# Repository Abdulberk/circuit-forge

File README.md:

<div align="center">

# ⚡ Circuit Forge

**AI-assisted circuit design, verified by real SPICE.**
Every verdict is backed by measured evidence — never by a model's say-so.

[Quick start](#-quick-start) · [What it does](#-what-it-does) · [Architecture](#%EF%B8%8F-architecture) · [Quality](#-tested-against-real-ngspice--in-ci) · [Docs](#-documentation) · [Status](#%EF%B8%8F-status--roadmap)

</div>

---

Most AI tools *tell* you a circuit works. **Circuit Forge proves it.** A design is only called
**verified** after real **ngspice** simulates it and every stated acceptance criterion is checked
against *measured* values — voltages, branch currents, cutoff frequency, THD, gain. What you get
back is not "looks good": it is an evidence pack.

```jsonc
// POST /verify-design → DesignEvidence (truncated)
{
  "verdict": "pass",
  "summary": "Simulation OK — 3/3 checks passed",
  "assertions": [
    {
      "label": "LED current ≈ 10 mA",
      "probe": "i(R1)", "metric": "final", "op": "approx",
      "target": 0.01, "actual": 0.0091, "pass": true,
      "detail": "final(i(R1)) = 0.0091 ✓ approx 0.01"
    }
    // …every criterion, with the measured value and its signed distance to target
  ],
  "measurements": [ { "node": "@r1[i]", "min": 0.0091, "max": 0.0091, "final": 0.0091 } /* … */ ],
  "robustness": {
    "worstCase": { "componentsCornered": ["R1"], "evaluated": 2, "passed": 2, "passAllCorners": true }
  }
}
```

> **Heads up — this repo is pnpm-only.** Internal packages use the `workspace:*` protocol, which
> `npm install` cannot parse. Always use `pnpm`. See [LOCAL_SETUP.md](LOCAL_SETUP.md).

---

## ✨ What it does

| | Capability |
|---|---|
| 🧠 **AI design loop** | Describe intent → the LLM designs against a **live parts catalog** (real MPNs + sourcing), simulates, reads the measured failures, and self-repairs until the spec is met — or honestly reports why not. |
| ✅ **Deterministic verification** | Circuit JSON → generated SPICE netlist → sandboxed ngspice → typed results → pass/fail per acceptance criterion (`min · max · final · pp · avg · rms · cutoff · thd · gain`). |
| 🎲 **Robustness, not just nominal** | Monte-Carlo yield with confidence interval, worst-case ±tolerance **corner analysis** (2ᵏ extremes), and parametric sweeps — a design that only works at nominal isn't a design. |
| 📈 **Broad analysis coverage** | Operating point, transient, AC, DC sweep, noise, DC sensitivity — plus Fourier/THD, `.meas` measurements, and small-signal transfer function. |
| 🔀 **Mixed-signal** | Digital XSPICE devices (gates, flip-flops, latches, tristate) auto-bridged to the analog domain. |
| 🔁 **SPICE interchange** | Import/export standard SPICE decks (LTspice/KiCad round-trip), analog and digital. |
| 🧩 **Real components** | TME-backed catalog search over 1.3M+ manufacturer parts (stock, pricing, datasheets), E-series (IEC 60063) value snapping, per-version **BOM** export. |
| 🖨️ **PCB pipeline** | Autorouted layout, KiCad-based DRC, Gerber / BOM / pick-and-place export, and a 3D board model (GLB) — as an async job queue. |
| 🏢 **Multi-tenant platform** | Orgs & RBAC, JWT auth, usage metering + quotas, platform-admin API with audit trail, OpenTelemetry observability (opt-in), readiness probes. |

---

## 🏗️ Architecture

The heart of the system is a **closed feedback cycle**: design → simulate → measure → repair.
Every netlist runs in a **sandboxed subprocess** — non-root, resource-limited, no network, hard timeout —
so a hostile or degenerate circuit can burn only its own cage. Batch work (queued simulations, Monte-Carlo,
corner sweeps) runs in a dedicated worker; the synchronous AI verify loop and `/verify-design` spawn ngspice
inside the API process under the same rlimit sandbox.

```mermaid
flowchart LR
    U["Circuit JSON<br/>+ acceptance criteria"] --> API["API<br/>(NestJS)"]
    P["Design prompt"] -.-> LLM["AI design loop<br/>(parts-grounded)"]
    LLM -.->|"proposes circuit"| API
    API -->|"enqueue"| Q[("BullMQ<br/>queue")]
    Q --> W["Simulation worker"]
    W --> NG["ngspice<br/>sandboxed subprocess"]
    NG --> W
    W --> DB[("Postgres / S3")]
    API -->|"poll"| DB
    API --> EV["Evidence pack:<br/>verdict · measurements · robustness"]
    EV -.->|"measured failures feed back"| LLM
```

Monorepo layout (pnpm + Turborepo):

```
apps/
  api/          NestJS REST API — auth, orgs, projects, simulation, AI generation, parts, usage
  worker-sim/   Simulation worker — sandboxed ngspice, Monte-Carlo / corner / sweep batch runners
  pcb-worker/   PCB worker — layout, DRC, Gerber/BOM/PnP, 3D model jobs
  pcb-viewer/   Dev tool — 3D board preview
packages/
  eda-core/     The EDA brain — circuit model, netlist generation, SPICE sanitization, ERC,
                result parsing, assertions, Monte-Carlo/corner/sweep engines  (MIT)
  llm-core/     AI design loop — parts-grounded tool use, simulate-in-the-loop self-repair
  pcb-core/     PCB contracts — fab profiles, DRC oracle, Gerber/BOM/PnP writers
crates/
  pcb-placement-rs/  Rust placement engine (cf-pcb-place) — out-of-process, ~100× on dense boards
```

Deep dive — services, queues, sandbox model, graceful shutdown, environment variables:
[docs/ARCHITECTURE.md](docs/ARCHITECTURE.md).

---

## 🔬 Tested against real ngspice — in CI

Unit tests alone are not enough for an EDA tool: the bugs live at the **circuit-to-SPICE
boundary** and in **simulator version drift**. So besides the per-package unit and integration
suites, every PR runs a real-ngspice regression battery:

| Harness | What it locks down |
|---|---|
| **Coverage matrix** — 83 cells | Every device × analysis × probe-form combination, checked against analytic expectations |
| **Edge battery** — 51 cases | Numeric limits, convergence, safety invariants, physics sanity |
| **Pairwise sweep** — 200 combos | Parameter × hostile-name interactions |
| **Seeded fuzz** | Random circuits must fail *loudly* or produce finite data — never silently wrong |

The engine itself is **pinned and drift-guarded**: CI asserts the runner's ngspice major, and a
dedicated job runs the same battery against the **exact Alpine binary production ships** — so an
engine upgrade is an explicit, matrix-verified decision, never a silent change.

---

## 🚀 Quick start

> Verified step-by-step instructions (incl. Windows specifics and port-conflict handling) live in
> **[LOCAL_SETUP.md](LOCAL_SETUP.md)**.

```powershell
cp .env.example .env                        # REQUIRED — .env is gitignored; the API refuses to boot
                                            # without two distinct 32+ char JWT secrets
pnpm install                                # never `npm install`
docker compose up -d postgres redis minio create-bucket   # create-bucket is NOT optional: nothing else
                                            # creates the S3 bucket, and /health/ready 503s without it
pnpm db:migrate:dev                         # apply schema (needs DATABASE_URL visible to apps/api —
                                            # see LOCAL_SETUP.md if it fails with Prisma P1012)
pnpm db:seed                                # demo data (optional)
pnpm dev                                    # start all apps in watch mode
```

- **API:** http://localhost:3000 · **Swagger:** http://localhost:3000/docs  (port from `PORT` in `.env`)
- **MinIO console:** http://localhost:9001 (`minioadmin` / `minioadmin`)
- **Demo login:** `demo@circuitforge.io` / `demo123456`

**ngspice** (required for actual simulation results):

```powershell
# Windows (Administrator PowerShell)
choco install ngspice -y
# Linux:  sudo apt-get install ngspice     |     macOS:  brew install ngspice
```

<details>
<summary><b>Root scripts</b></summary>

| Script | Purpose |
|---|---|
| `pnpm dev` / `pnpm build` | Watch mode / build all (Turbo) |
| `pnpm test` / `test:cov` / `test:e2e` | Unit + integration suites |
| `pnpm test:matrix` / `test:edge` / `test:sweep` / `test:fuzz` | Real-ngspice regression battery |
| `pnpm test:robustness` | Monte-Carlo/corner current-criteria proof (real ngspice) |
| `pnpm test:layout` | PCB layout + DRC eval harness (real freerouting + kicad-cli) |
| `pnpm test:tier` | Robustness-tier reachability proof (real ngspice) |
| `pnpm typecheck` / `lint` / `format` | Static checks |
| `pnpm db:migrate` / `db:generate` / `db:seed` / `db:studio` | Database workflows |

</details>

---

## 📚 Documentation

| Doc | Contents |
|---|---|
| [docs/ARCHITECTURE.md](docs/ARCHITECTURE.md) | System design, environment variables, queues, sandbox |
| [docs/API.md](docs/API.md) | Full endpoint reference |
| [docs/EDA_CORE.md](docs/EDA_CORE.md) | Circuit model, netlist generation, analyses |
| [docs/OBSERVABILITY.md](docs/OBSERVABILITY.md) | OpenTelemetry setup (opt-in, inert by default) |
| [VERIFICATION.md](VERIFICATION.md) | What "verified" means here, and how it is enforced |
| [LOCAL_SETUP.md](LOCAL_SETUP.md) | Verified local setup, Windows gotchas |

---

## 🗺️ Status & roadmap

**Current: [v0.1.0](https://github.com/Abdulberk/circuit-forge/releases) (pre-release).** This is
the backend milestone — honest about what it is:

- ✅ Simulation, verification, robustness, AI loop, PCB pipeline, multi-tenant platform — built and tested
- 🚧 Web frontend — in progress (this repo is backend + API today)
- 🚧 Security hardening for hostile multi-tenant traffic — deferred, tracked
- 🚧 Load testing & production deployment — not yet

APIs may change before 1.0.

## 📄 License

[`@circuit-forge/eda-core`](packages/eda-core/LICENSE) is **MIT** and published on
[npm](https://www.npmjs.com/package/@circuit-forge/eda-core) (from this monorepo — see
`packages/eda-core`). The remaining packages and applications are **not yet licensed**
(all rights reserved) while the project is pre-release — licensing will be finalized before 1.0.

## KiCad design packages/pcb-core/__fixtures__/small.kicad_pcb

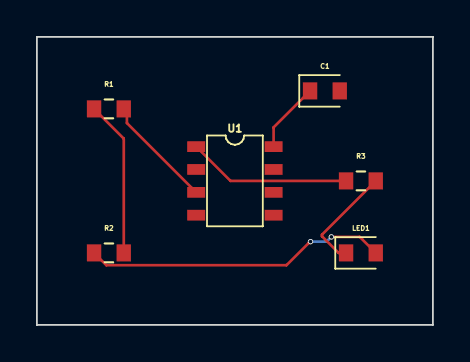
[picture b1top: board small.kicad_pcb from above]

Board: 2 copper layers, 22.0 x 16.0 mm, 6 parts (0 on the bottom side), 6 nets.

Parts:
C1: 100nF; capacitor_0603
LED1: LED; led_0603
R1, R2: 10kΩ; resistor_res0603
R3: 330Ω; resistor_res0603
U1: chip_soic8

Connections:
.LED1 > .cathode to .R2 > .pin1: LED1.2, R2.1
.R1 > .pin1 to .R2 > .pin2: R1.1, R2.2
.R1 > .pin2 to .U1 > .pin3: R1.2, U1.3
.R3 > .pin2 to .LED1 > .anode: LED1.1, R3.2
.U1 > .pin1 to .R3 > .pin1: R3.1, U1.1
.U1 > .pin8 to .C1 > .pin1: C1.1, U1.8
